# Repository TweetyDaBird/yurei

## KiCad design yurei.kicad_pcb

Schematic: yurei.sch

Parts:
C9: 4u7; C_0603_1608Metric; Manufacturer_Part_Number 06035C104JAT2A; Mouser Part Number 581-06035C104JAT2A
C10: C_Small; C_0805_2012Metric
C11: 22nF; C_0805_2012Metric
D1, D2, D3, D4, D5, D6, D7, D8, D9, D10, D11, D12, D13, D14, D15, D16, D17, D18, D19, D20, D21, D22, D23, D24, D25, D26, D27, D28, D29, D30, D31, D32, D33, D34, D35, D36, D37, D38, D39, D40, D41, D42, D43, D44, D45, D46, D47, D48, D49, D50, D51, D52, D53, D54, D55, D56, D57, D58, D59, D60, D61, D62, D63, D64, D65, D66, D67, D68, D69, D70, D71, D72, D73, D74, D75, D76, D77, D78, D79, D80, D81, D82, D83, D84, D85, D86, D87, D89: 1N4148W; D_SOD-123
D88: NSR0340HT1G; D_SOD-323; Manufacturer_Part_Number NSR0240HT1G
FT1: SI2301CDS-T1-GE3; SOT-23; Mouser Part Number 771-NX2301P215
H1: MountingHole_Pad; MountingHole_2.7mm_M2.5_DIN965_Pad
J1: Conn_01x02; PinHeader_1x02_P2.54mm_Vertical
J2: Conn_01x05; PinHeader_1x05_P2.54mm_Vertical
L1: L; L_0805_2012Metric
P1: USB_C_USB2.0; HRO-TYPE-C-31-M-12-Assembly
R1, R2: 5k1; R_0805_2012Metric_Pad1.15x1.40mm_HandSolder
R3: 1M; R_0805_2012Metric_Pad1.15x1.40mm_HandSolder
R5: 3K3; R_0402_1005Metric; Manufacturer_Part_Number 0402WGF3301TCE
R8: 10M; R_0402_1005Metric; Manufacturer_Part_Number 0402WGF3301TCE
R9: 2M2; R_0402_1005Metric; Manufacturer_Part_Number 0402WGF3301TCE
SW1, SW2, SW3, SW4, SW5, SW6, SW7, SW8, SW9, SW10, SW11, SW12, SW13, SW14, SW15, SW16, SW17, SW18, SW19, SW20, SW21, SW22, SW23, SW24, SW25, SW26, SW27, SW28, SW29, SW30, SW31, SW32, SW33, SW34, SW35, SW36, SW37, SW38, SW39, SW40, SW41, SW42, SW43, SW44, SW45, SW46, SW47, SW48, SW49, SW50, SW51, SW52, SW53, SW54, SW55, SW56, SW57, SW58, SW59, SW60, SW61, SW62, SW63, SW64, SW65, SW66, SW67, SW68, SW69, SW70, SW71, SW72, SW73, SW74, SW75, SW76, SW77, SW78, SW79, SW80, SW81, SW82, SW83, SW84, SW85, SW86, SW87, SW89, SW90: SW_SPST; Kailh_socket_MX_RGB
SW88: SW_Push
U1: TP4056_Charger; T4056 1A Charge
U3: E73-2G4M08S1C-52840

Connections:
BATT_MON: C11.1, R8.1, R9.1, U3.18
Batt+: J1.1, R8.2, U1.5 (Batt+)
Batt-: J1.2, U1.4 (Batt-)
Col0: SW1.1, SW17.1, SW34.1, SW51.1, SW64.1, SW77.1, SW90.2, U3.6
Col1: SW18.1, SW35.1, SW52.1, SW78.1, SW89.1, U3.7
Col2: SW2.1, SW19.1, SW36.1, SW53.1, SW65.1, SW79.1, U3.8
Col3: SW3.1, SW20.1, SW37.1, SW54.1, SW66.1, U3.9
Col4: SW4.1, SW21.1, SW38.1, SW55.1, SW67.1, U3.10
Col5: SW5.1, SW22.1, SW39.1, SW56.1, SW68.1, U3.20
Col6: SW6.1, SW23.1, SW40.1, SW57.1, SW69.1, SW80.1, U3.11
Col7: SW7.1, SW24.1, SW41.1, SW58.1, SW70.1, U3.12
Col8: SW8.1, SW25.1, SW42.1, SW59.1, SW71.1, U3.13
Col9: SW9.1, SW26.1, SW43.1, SW60.1, SW72.1, U3.14
Col10: SW10.1, SW27.1, SW44.1, SW61.1, SW73.1, SW81.1, U3.15
Col11: SW11.1, SW28.1, SW45.1, SW62.1, SW74.1, SW82.1, U3.16
Col12: SW12.1, SW29.1, SW46.1, SW75.1, SW83.1, U3.17
Col13: SW13.1, SW30.1, SW47.1, SW63.1, SW84.1, U3.4
Col14: SW14.1, SW31.1, SW48.1, SW85.1, U3.3
Col15: SW15.1, SW32.1, SW49.1, SW76.1, SW86.1, U3.2
Col16: SW16.1, SW33.1, SW50.1, SW87.1, U3.1
D+: P1.A6 (D+), P1.B6 (D+), U3.31
D-: P1.A7 (D-), P1.B7 (D-), U3.29
I2C+: U3.43; also elsewhere on the board
I2C-: U3.42; also elsewhere on the board
INTB: U3.41; also elsewhere on the board
Load: FT1.3 (D), U1.6 (Load+)
unnamed: D1.2, SW1.2
unnamed: D2.2, SW2.2
unnamed: D3.2, SW3.2
unnamed: D4.2, SW4.2
unnamed: D5.2, SW5.2
unnamed: D6.2, SW6.2
unnamed: D7.2, SW7.2
unnamed: D8.2, SW8.2
unnamed: D9.2, SW9.2
unnamed: D10.2, SW10.2
unnamed: D11.2, SW11.2
unnamed: D12.2, SW12.2
unnamed: D13.2, SW13.2
unnamed: D14.2, SW14.2
unnamed: D15.2, SW15.2
unnamed: D16.2, SW16.2
unnamed: D17.2, SW17.2
unnamed: D18.2, SW18.2
unnamed: D19.2, SW19.2
unnamed: D20.2, SW20.2
unnamed: D21.2, SW21.2
unnamed: D22.2, SW22.2
unnamed: D23.2, SW23.2
unnamed: D24.2, SW24.2
unnamed: D25.2, SW25.2
unnamed: D26.2, SW26.2
unnamed: D27.2, SW27.2
unnamed: D28.2, SW28.2
unnamed: D29.2, SW29.2
unnamed: D30.2, SW30.2
unnamed: D31.2, SW31.2
unnamed: D32.2, SW32.2
unnamed: D33.2, SW33.2
unnamed: D34.2, SW34.2
unnamed: D35.2, SW35.2
unnamed: D36.2, SW36.2
unnamed: D37.2 (A), SW37.2
unnamed: D38.2, SW38.2
unnamed: D39.2, SW39.2
unnamed: D40.2, SW40.2
unnamed: D41.2, SW41.2
unnamed: D42.2, SW42.2
unnamed: D43.2, SW43.2
unnamed: D44.2, SW44.2
unnamed: D45.2, SW45.2
unnamed: D46.2, SW46.2
unnamed: D47.2, SW47.2
unnamed: D48.2, SW48.2
unnamed: D49.2, SW49.2
unnamed: D50.2, SW50.2
unnamed: D51.2, SW51.2
unnamed: D52.2, SW52.2
unnamed: D53.2, SW53.2
unnamed: D54.2, SW54.2
unnamed: D55.2, SW55.2
unnamed: D56.2, SW56.2
unnamed: D57.2, SW57.2
unnamed: D58.2, SW58.2
unnamed: D59.2, SW59.2
unnamed: D60.2, SW60.2
unnamed: D61.2, SW61.2
unnamed: D62.2, SW62.2
unnamed: D63.2, SW63.2
unnamed: D64.2, SW64.2, SW90.1
unnamed: D65.2, SW65.2
unnamed: D66.2, SW66.2
unnamed: D67.2, SW67.2
unnamed: D68.2, SW68.2
unnamed: D69.2, SW69.2
unnamed: D70.2, SW70.2
unnamed: D71.2, SW71.2
unnamed: D72.2, SW72.2
unnamed: D73.2, SW73.2
unnamed: D74.2, SW74.2
unnamed: D75.2, SW75.2
unnamed: D76.2, SW76.2
unnamed: D77.2, SW77.2
unnamed: D78.2, SW78.2
unnamed: D79.2, SW79.2
unnamed: D80.2, SW80.2
unnamed: D81.2, SW81.2
unnamed: D82.2, SW82.2
unnamed: D83.2, SW83.2
unnamed: D84.2, SW84.2
unnamed: D85.2, SW85.2
unnamed: D86.2, SW86.2
unnamed: D87.2, SW87.2
unnamed: D89.2, SW89.2
unnamed: L1.2, U3.25
unnamed: P1.A5 (CC1), R1.2
unnamed: P1.B5 (CC2), R2.2
PWR: D88.1 (K), FT1.2 (S), U3.23; also elsewhere on the board
Reset: J2.4, SW88.1, U3.26
Row0: D1.1, D2.1, D3.1, D4.1, D5.1, D6.1, D7.1, D8.1, D9.1, D10.1, D11.1, D12.1, D13.1, D14.1, D15.1, D16.1, U3.30
Row1: D17.1, D18.1, D19.1, D20.1, D21.1, D22.1, D23.1, D24.1, D25.1, D26.1, D27.1, D28.1, D29.1, D30.1, D31.1, D32.1, D33.1, U3.32
Row2: D34.1, D35.1, D36.1, D37.1 (K), D38.1, D39.1, D40.1, D41.1, D42.1, D43.1, D44.1, D45.1, D46.1, D47.1, D48.1, D49.1, D50.1, U3.28
Row3: D51.1, D52.1, D53.1, D54.1, D55.1, D56.1, D57.1, D58.1, D59.1, D60.1, D61.1, D62.1, D63.1, U3.34
Row4: D64.1, D65.1, D66.1, D67.1, D68.1, D69.1, D70.1, D71.1, D72.1, D73.1, D74.1, D75.1, D76.1, D89.1, U3.38
Row5: D77.1, D78.1, D79.1, D80.1, D81.1, D82.1, D83.1, D84.1, D85.1, D86.1, D87.1, U3.36
SDB: U3.40; also elsewhere on the board
SHIELD: C9.1, H1.1, P1.S1 (SHIELD), R3.2
SWDCLK: J2.2, U3.39
SWDIO: J2.3, U3.37
VBUS: D88.2 (A), FT1.1 (G), P1.A4 (VBUS), P1.A9 (VBUS), P1.B4 (VBUS), P1.B9 (VBUS), R5.1, U1.1 (+5V), U3.27
V_IO: C10.1, J2.5, L1.1, U3.19; also elsewhere on the board

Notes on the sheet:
Battery charge/protection module (100/500/1000mA)
Footprint needs to be confirmed!
If case and/or plate is conductive, connect to shield for ESD/EMC protection. NOTE! Full metal case is NOT recommended for wireless/BT operation!
Power selector, isolates battery and charger from main circuit when USB cable is inserted.
separate power from charger with zener? diode (no backfeed!) switch??? för BT vs WL2.4Ghz
Rprog 10k - 130mA 5k - 250mA 4k - 300mA 3k - 400mA 2k - 580mA 1,66 - 690mA 1,5k - 780mA 1,33 - 900mA 1,2k - 1000mA
Battery voltage monitor
J-Link connector
Reset switch

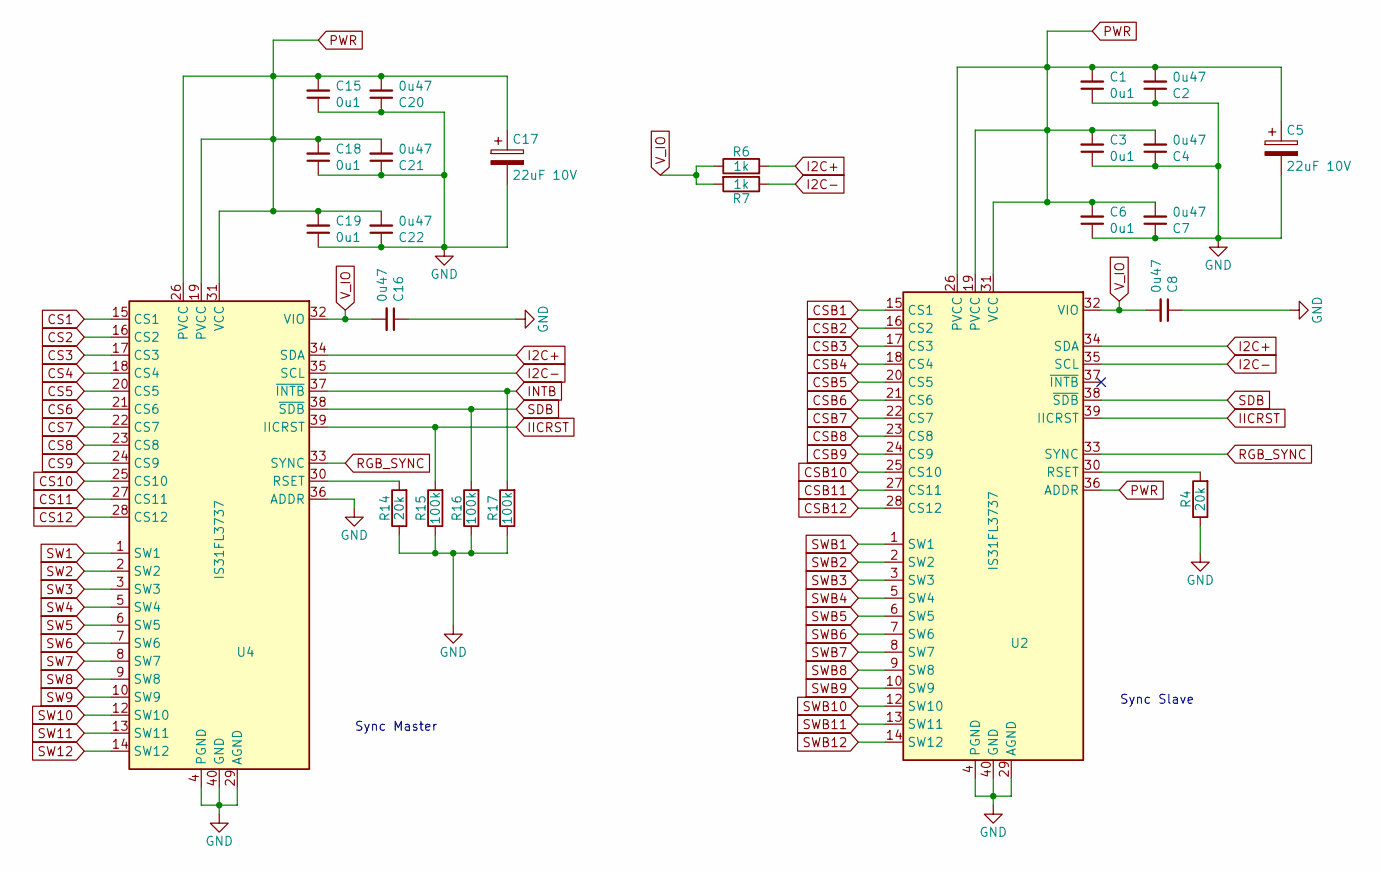
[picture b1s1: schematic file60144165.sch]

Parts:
C1, C3, C6, C15, C18, C19: 0u1; C_0603_1608Metric; Manufacturer_Part_Number 06035C104JAT2A; Mouser Part Number 581-06035C104JAT2A
C2, C4, C7, C8, C16, C20, C21, C22: 0u47; C_0603_1608Metric; Manufacturer_Part_Number UMK107B7474KA-TR; Mouser Part Number 963-UMK107B7474KA-TR
C5, C17: 22uF 10V; CP_EIA-3216-18_Kemet-A; Manufacturer_Part_Number TPSA226K010T0900; Mouser Part Number 581-TPSA226K010T0900
R4, R14: 20k; R_0603_1608Metric; Manufacturer_Part_Number ERJ-3GEYJ203V; Mouser Part Number 667-ERJ-3GEYJ203V
R6, R7: 1k; R_0603_1608Metric; Manufacturer_Part_Number ERJ-3EKF1003V; Mouser Part Number 667-ERJ-3EKF1003V
R15, R16, R17: 100k; R_0603_1608Metric; Manufacturer_Part_Number ERJ-3EKF1003V; Mouser Part Number 667-ERJ-3EKF1003V
U2, U4: IS31FL3737; QFN-40-1EP_5x5mm_P0.4mm_EP3.8x3.8mm_ThermalVias; Mouser Part Number 870-IS31FL3733-TQLS4

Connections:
CS1: U4.15 (CS1); also elsewhere on the board
CS2: U4.16 (CS2); also elsewhere on the board
CS3: U4.17 (CS3); also elsewhere on the board
CS4: U4.18 (CS4); also elsewhere on the board
CS5: U4.20 (CS5); also elsewhere on the board
CS6: U4.21 (CS6); also elsewhere on the board
CS7: U4.22 (CS7); also elsewhere on the board
CS8: U4.23 (CS8); also elsewhere on the board
CS9: U4.24 (CS9); also elsewhere on the board
CS10: U4.25 (CS10); also elsewhere on the board
CS11: U4.27 (CS11); also elsewhere on the board
CS12: U4.28 (CS12); also elsewhere on the board
CSB1: U2.15 (CS1); also elsewhere on the board
CSB2: U2.16 (CS2); also elsewhere on the board
CSB3: U2.17 (CS3); also elsewhere on the board
CSB4: U2.18 (CS4); also elsewhere on the board
CSB5: U2.20 (CS5); also elsewhere on the board
CSB6: U2.21 (CS6); also elsewhere on the board
CSB7: U2.22 (CS7); also elsewhere on the board
CSB8: U2.23 (CS8); also elsewhere on the board
CSB9: U2.24 (CS9); also elsewhere on the board
CSB10: U2.25 (CS10); also elsewhere on the board
CSB11: U2.27 (CS11); also elsewhere on the board
CSB12: U2.28 (CS12); also elsewhere on the board
I2C+: R6.2, U2.34 (SDA), U4.34 (SDA); also elsewhere on the board
I2C-: R7.1, U2.35 (SCL), U4.35 (SCL); also elsewhere on the board
IICRST: R15.2, U2.39 (IICRST), U4.39 (IICRST)
INTB: R17.2, U4.37 (~INTB); also elsewhere on the board
unnamed: R4.2, U2.30 (RSET)
unnamed: R14.2, U4.30 (RSET)
PWR: C1.2, C2.2, C3.2, C4.2, C5.1, C6.2, C7.2, C15.2, C17.1, C18.2, C19.2, C20.2, C21.2, C22.2, U2.19 (PVCC), U2.26 (PVCC), U2.31 (VCC), U2.36 (ADDR), U4.19 (PVCC), U4.26 (PVCC), U4.31 (VCC); also elsewhere on the board
RGB_SYNC: U2.33 (SYNC), U4.33 (SYNC)
SDB: R16.2, U2.38 (~SDB), U4.38 (~SDB); also elsewhere on the board
SW1: U4.1 (SW1); also elsewhere on the board
SW2: U4.2 (SW2); also elsewhere on the board
SW3: U4.3 (SW3); also elsewhere on the board
SW4: U4.5 (SW4); also elsewhere on the board
SW5: U4.6 (SW5); also elsewhere on the board
SW6: U4.7 (SW6); also elsewhere on the board
SW7: U4.8 (SW7); also elsewhere on the board
SW8: U4.9 (SW8); also elsewhere on the board
SW9: U4.10 (SW9); also elsewhere on the board
SW10: U4.12 (SW10); also elsewhere on the board
SW11: U4.13 (SW11); also elsewhere on the board
SW12: U4.14 (SW12); also elsewhere on the board
SWB1: U2.1 (SW1); also elsewhere on the board
SWB2: U2.2 (SW2); also elsewhere on the board
SWB3: U2.3 (SW3); also elsewhere on the board
SWB4: U2.5 (SW4); also elsewhere on the board
SWB5: U2.6 (SW5); also elsewhere on the board
SWB6: U2.7 (SW6); also elsewhere on the board
SWB7: U2.8 (SW7); also elsewhere on the board
SWB8: U2.9 (SW8); also elsewhere on the board
SWB9: U2.10 (SW9); also elsewhere on the board
SWB10: U2.12 (SW10); also elsewhere on the board
SWB11: U2.13 (SW11); also elsewhere on the board
SWB12: U2.14 (SW12); also elsewhere on the board
V_IO: C8.2, C16.2, R6.1, R7.2, U2.32 (VIO), U4.32 (VIO); also elsewhere on the board

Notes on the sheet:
Sync Master
Sync Slave

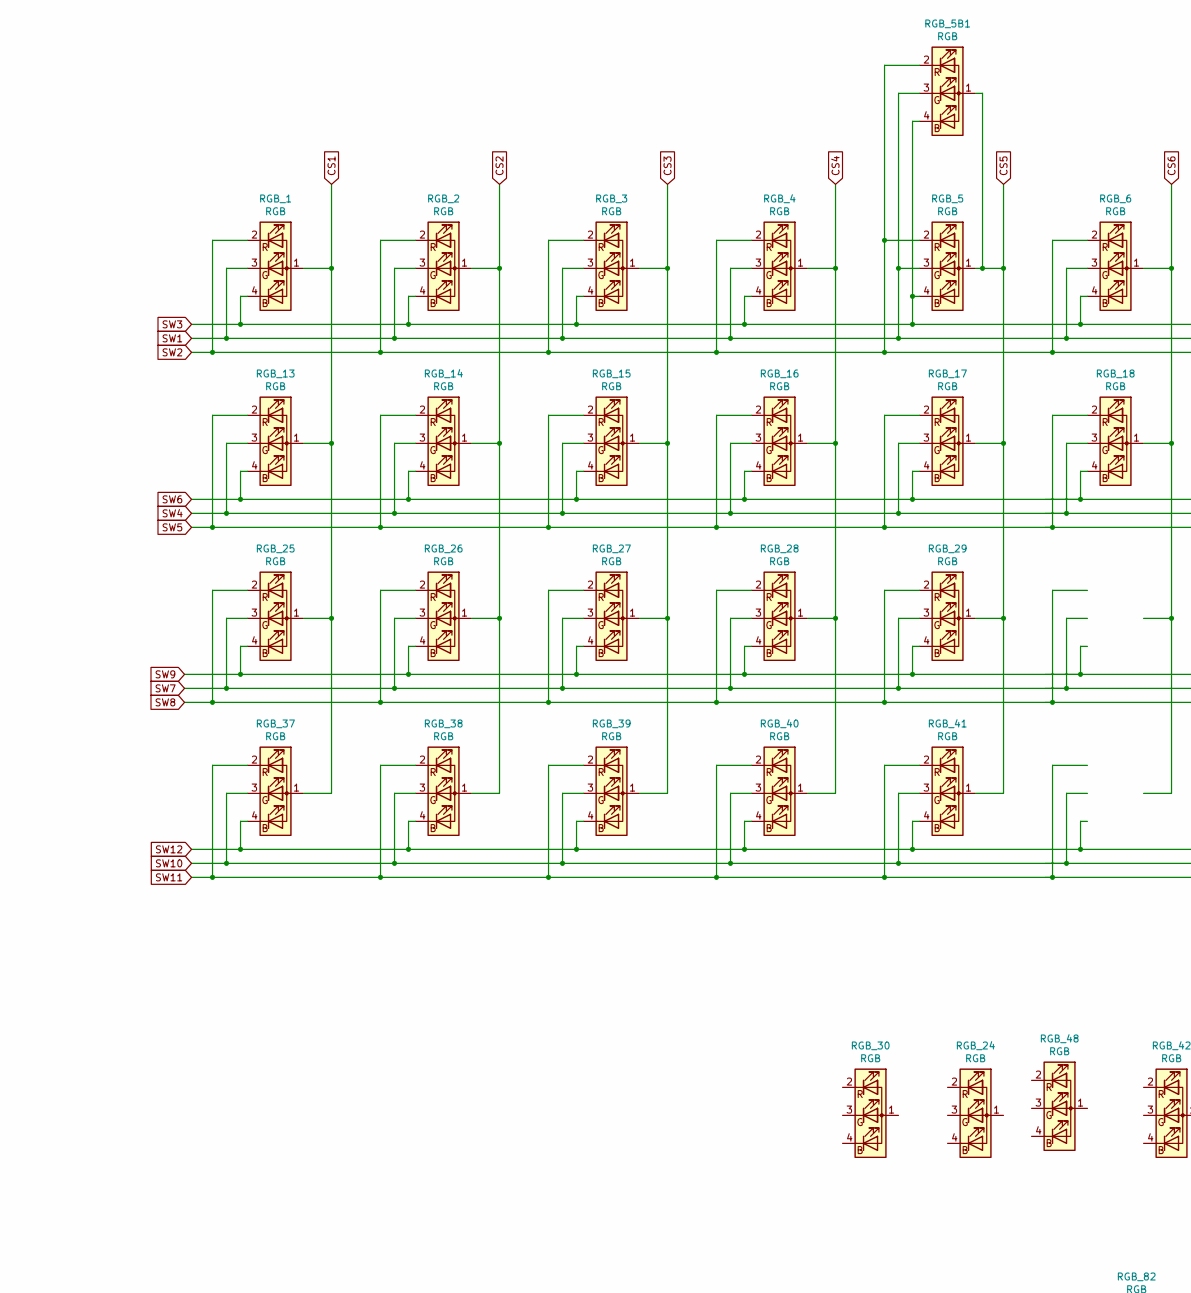
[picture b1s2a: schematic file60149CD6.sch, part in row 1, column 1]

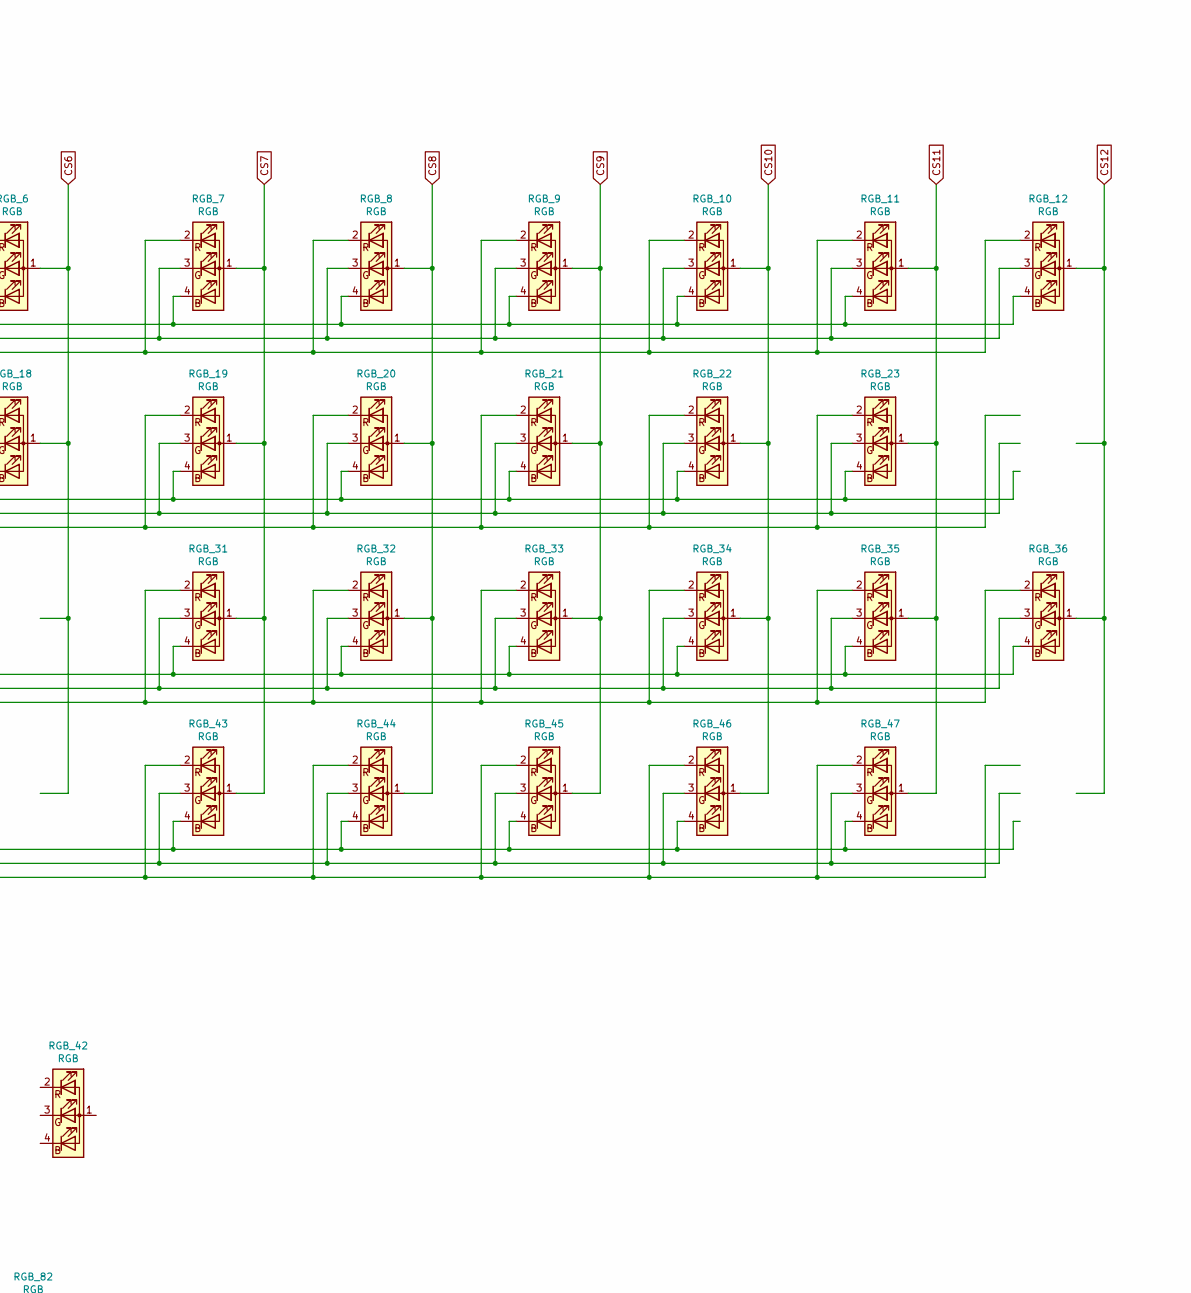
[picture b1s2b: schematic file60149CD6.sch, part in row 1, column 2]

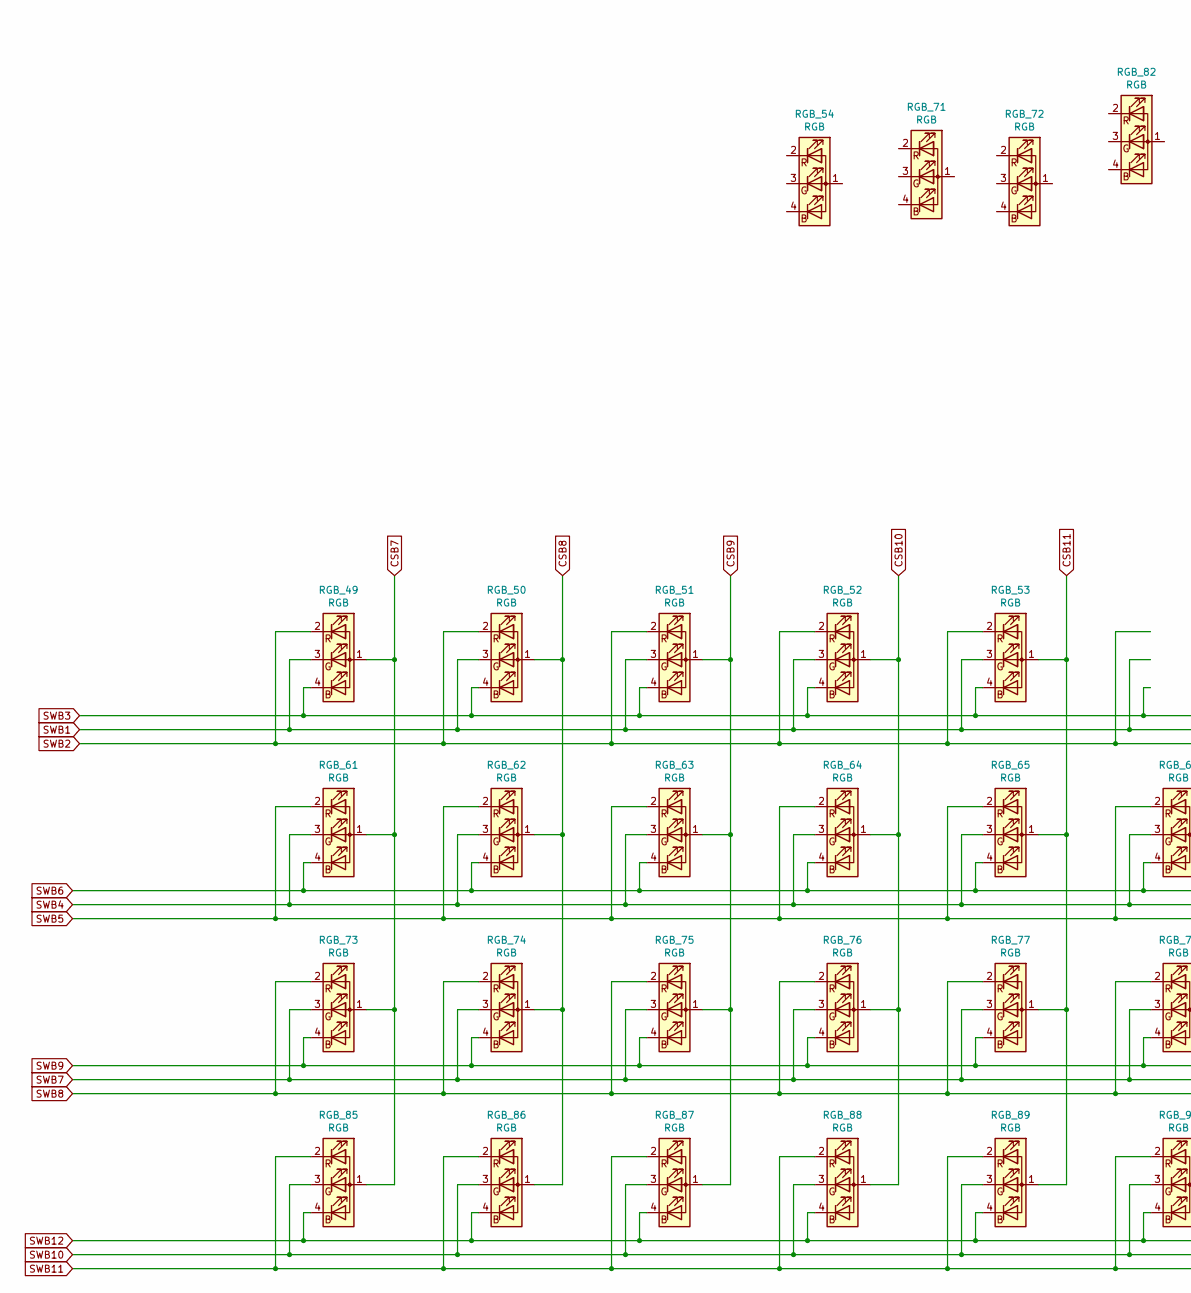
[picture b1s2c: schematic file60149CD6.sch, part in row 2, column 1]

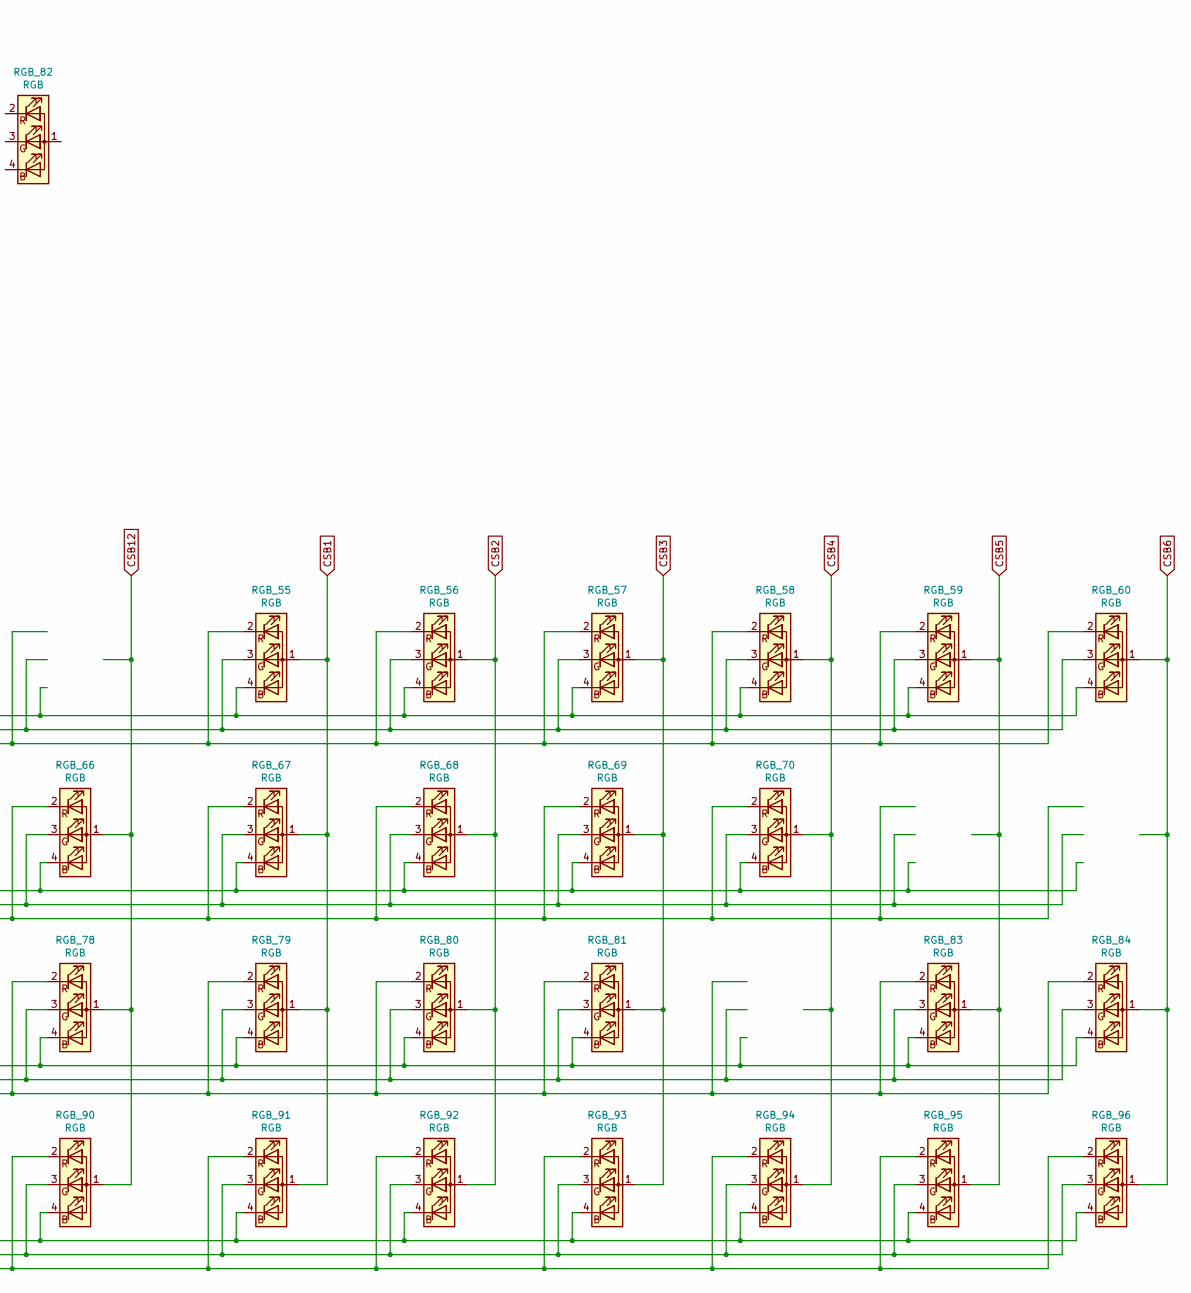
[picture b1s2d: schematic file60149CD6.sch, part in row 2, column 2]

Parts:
RGB_1, RGB_2, RGB_3, RGB_4, RGB_5, RGB_5B1, RGB_6, RGB_7, RGB_8, RGB_9, RGB_10, RGB_11, RGB_12, RGB_13, RGB_14, RGB_15, RGB_16, RGB_17, RGB_18, RGB_19, RGB_20, RGB_21, RGB_22, RGB_23, RGB_24, RGB_25, RGB_26, RGB_27, RGB_28, RGB_29, RGB_30, RGB_31, RGB_32, RGB_33, RGB_34, RGB_35, RGB_36, RGB_37, RGB_38, RGB_39, RGB_40, RGB_41, RGB_42, RGB_43, RGB_44, RGB_45, RGB_46, RGB_47, RGB_48, RGB_49, RGB_50, RGB_51, RGB_52, RGB_53, RGB_54, RGB_55, RGB_56, RGB_57, RGB_58, RGB_59, RGB_60, RGB_61, RGB_62, RGB_63, RGB_64, RGB_65, RGB_66, RGB_67, RGB_68, RGB_69, RGB_70, RGB_71, RGB_72, RGB_73, RGB_74, RGB_75, RGB_76, RGB_77, RGB_78, RGB_79, RGB_80, RGB_81, RGB_82, RGB_83, RGB_84, RGB_85, RGB_86, RGB_87, RGB_88, RGB_89, RGB_90, RGB_91, RGB_92, RGB_93, RGB_94, RGB_95, RGB_96: RGB; APTF1616SEEZGQBDC; Mouser Part Number 604-APTF1616SEJ3ZGGV

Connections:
CS1: RGB_1.1 (A), RGB_13.1 (A), RGB_25.1 (A), RGB_37.1 (A); also elsewhere on the board
CS2: RGB_2.1 (A), RGB_14.1 (A), RGB_26.1 (A), RGB_38.1 (A); also elsewhere on the board
CS3: RGB_3.1 (A), RGB_15.1 (A), RGB_27.1 (A), RGB_39.1 (A); also elsewhere on the board
CS4: RGB_4.1 (A), RGB_16.1 (A), RGB_28.1 (A), RGB_40.1 (A); also elsewhere on the board
CS5: RGB_5.1 (A), RGB_5B1.1 (A), RGB_17.1 (A), RGB_29.1 (A), RGB_41.1 (A); also elsewhere on the board
CS6: RGB_6.1 (A), RGB_18.1 (A); also elsewhere on the board
CS7: RGB_7.1 (A), RGB_19.1 (A), RGB_31.1 (A), RGB_43.1 (A); also elsewhere on the board
CS8: RGB_8.1 (A), RGB_20.1 (A), RGB_32.1 (A), RGB_44.1 (A); also elsewhere on the board
CS9: RGB_9.1 (A), RGB_21.1 (A), RGB_33.1 (A), RGB_45.1 (A); also elsewhere on the board
CS10: RGB_10.1 (A), RGB_22.1 (A), RGB_34.1 (A), RGB_46.1 (A); also elsewhere on the board
CS11: RGB_11.1 (A), RGB_23.1 (A), RGB_35.1 (A), RGB_47.1 (A); also elsewhere on the board
CS12: RGB_12.1 (A), RGB_36.1 (A); also elsewhere on the board
CSB1: RGB_55.1 (A), RGB_67.1 (A), RGB_79.1 (A), RGB_91.1 (A); also elsewhere on the board
CSB2: RGB_56.1 (A), RGB_68.1 (A), RGB_80.1 (A), RGB_92.1 (A); also elsewhere on the board
CSB3: RGB_57.1 (A), RGB_69.1 (A), RGB_81.1 (A), RGB_93.1 (A); also elsewhere on the board
CSB4: RGB_58.1 (A), RGB_70.1 (A), RGB_94.1 (A); also elsewhere on the board
CSB5: RGB_59.1 (A), RGB_83.1 (A), RGB_95.1 (A); also elsewhere on the board
CSB6: RGB_60.1 (A), RGB_84.1 (A), RGB_96.1 (A); also elsewhere on the board
CSB7: RGB_49.1 (A), RGB_61.1 (A), RGB_73.1 (A), RGB_85.1 (A); also elsewhere on the board
CSB8: RGB_50.1 (A), RGB_62.1 (A), RGB_74.1 (A), RGB_86.1 (A); also elsewhere on the board
CSB9: RGB_51.1 (A), RGB_63.1 (A), RGB_75.1 (A), RGB_87.1 (A); also elsewhere on the board
CSB10: RGB_52.1 (A), RGB_64.1 (A), RGB_76.1 (A), RGB_88.1 (A); also elsewhere on the board
CSB11: RGB_53.1 (A), RGB_65.1 (A), RGB_77.1 (A), RGB_89.1 (A); also elsewhere on the board
CSB12: RGB_66.1 (A), RGB_78.1 (A), RGB_90.1 (A); also elsewhere on the board
SW1: RGB_1.3 (GK), RGB_2.3 (GK), RGB_3.3 (GK), RGB_4.3 (GK), RGB_5.3 (GK), RGB_5B1.3 (GK), RGB_6.3 (GK), RGB_7.3 (GK), RGB_8.3 (GK), RGB_9.3 (GK), RGB_10.3 (GK), RGB_11.3 (GK), RGB_12.3 (GK); also elsewhere on the board
SW2: RGB_1.2 (RK), RGB_2.2 (RK), RGB_3.2 (RK), RGB_4.2 (RK), RGB_5.2 (RK), RGB_5B1.2 (RK), RGB_6.2 (RK), RGB_7.2 (RK), RGB_8.2 (RK), RGB_9.2 (RK), RGB_10.2 (RK), RGB_11.2 (RK), RGB_12.2 (RK); also elsewhere on the board
SW3: RGB_1.4 (BK), RGB_2.4 (BK), RGB_3.4 (BK), RGB_4.4 (BK), RGB_5.4 (BK), RGB_5B1.4 (BK), RGB_6.4 (BK), RGB_7.4 (BK), RGB_8.4 (BK), RGB_9.4 (BK), RGB_10.4 (BK), RGB_11.4 (BK), RGB_12.4 (BK); also elsewhere on the board
SW4: RGB_13.3 (GK), RGB_14.3 (GK), RGB_15.3 (GK), RGB_16.3 (GK), RGB_17.3 (GK), RGB_18.3 (GK), RGB_19.3 (GK), RGB_20.3 (GK), RGB_21.3 (GK), RGB_22.3 (GK), RGB_23.3 (GK); also elsewhere on the board
SW5: RGB_13.2 (RK), RGB_14.2 (RK), RGB_15.2 (RK), RGB_16.2 (RK), RGB_17.2 (RK), RGB_18.2 (RK), RGB_19.2 (RK), RGB_20.2 (RK), RGB_21.2 (RK), RGB_22.2 (RK), RGB_23.2 (RK); also elsewhere on the board
SW6: RGB_13.4 (BK), RGB_14.4 (BK), RGB_15.4 (BK), RGB_16.4 (BK), RGB_17.4 (BK), RGB_18.4 (BK), RGB_19.4 (BK), RGB_20.4 (BK), RGB_21.4 (BK), RGB_22.4 (BK), RGB_23.4 (BK); also elsewhere on the board
SW7: RGB_25.3 (GK), RGB_26.3 (GK), RGB_27.3 (GK), RGB_28.3 (GK), RGB_29.3 (GK), RGB_31.3 (GK), RGB_32.3 (GK), RGB_33.3 (GK), RGB_34.3 (GK), RGB_35.3 (GK), RGB_36.3 (GK); also elsewhere on the board
SW8: RGB_25.2 (RK), RGB_26.2 (RK), RGB_27.2 (RK), RGB_28.2 (RK), RGB_29.2 (RK), RGB_31.2 (RK), RGB_32.2 (RK), RGB_33.2 (RK), RGB_34.2 (RK), RGB_35.2 (RK), RGB_36.2 (RK); also elsewhere on the board
SW9: RGB_25.4 (BK), RGB_26.4 (BK), RGB_27.4 (BK), RGB_28.4 (BK), RGB_29.4 (BK), RGB_31.4 (BK), RGB_32.4 (BK), RGB_33.4 (BK), RGB_34.4 (BK), RGB_35.4 (BK), RGB_36.4 (BK); also elsewhere on the board
SW10: RGB_37.3 (GK), RGB_38.3 (GK), RGB_39.3 (GK), RGB_40.3 (GK), RGB_41.3 (GK), RGB_43.3 (GK), RGB_44.3 (GK), RGB_45.3 (GK), RGB_46.3 (GK), RGB_47.3 (GK); also elsewhere on the board
SW11: RGB_37.2 (RK), RGB_38.2 (RK), RGB_39.2 (RK), RGB_40.2 (RK), RGB_41.2 (RK), RGB_43.2 (RK), RGB_44.2 (RK), RGB_45.2 (RK), RGB_46.2 (RK), RGB_47.2 (RK); also elsewhere on the board
SW12: RGB_37.4 (BK), RGB_38.4 (BK), RGB_39.4 (BK), RGB_40.4 (BK), RGB_41.4 (BK), RGB_43.4 (BK), RGB_44.4 (BK), RGB_45.4 (BK), RGB_46.4 (BK), RGB_47.4 (BK); also elsewhere on the board
SWB1: RGB_49.3 (GK), RGB_50.3 (GK), RGB_51.3 (GK), RGB_52.3 (GK), RGB_53.3 (GK), RGB_55.3 (GK), RGB_56.3 (GK), RGB_57.3 (GK), RGB_58.3 (GK), RGB_59.3 (GK), RGB_60.3 (GK); also elsewhere on the board
SWB2: RGB_49.2 (RK), RGB_50.2 (RK), RGB_51.2 (RK), RGB_52.2 (RK), RGB_53.2 (RK), RGB_55.2 (RK), RGB_56.2 (RK), RGB_57.2 (RK), RGB_58.2 (RK), RGB_59.2 (RK), RGB_60.2 (RK); also elsewhere on the board
SWB3: RGB_49.4 (BK), RGB_50.4 (BK), RGB_51.4 (BK), RGB_52.4 (BK), RGB_53.4 (BK), RGB_55.4 (BK), RGB_56.4 (BK), RGB_57.4 (BK), RGB_58.4 (BK), RGB_59.4 (BK), RGB_60.4 (BK); also elsewhere on the board
SWB4: RGB_61.3 (GK), RGB_62.3 (GK), RGB_63.3 (GK), RGB_64.3 (GK), RGB_65.3 (GK), RGB_66.3 (GK), RGB_67.3 (GK), RGB_68.3 (GK), RGB_69.3 (GK), RGB_70.3 (GK); also elsewhere on the board
SWB5: RGB_61.2 (RK), RGB_62.2 (RK), RGB_63.2 (RK), RGB_64.2 (RK), RGB_65.2 (RK), RGB_66.2 (RK), RGB_67.2 (RK), RGB_68.2 (RK), RGB_69.2 (RK), RGB_70.2 (RK); also elsewhere on the board
SWB6: RGB_61.4 (BK), RGB_62.4 (BK), RGB_63.4 (BK), RGB_64.4 (BK), RGB_65.4 (BK), RGB_66.4 (BK), RGB_67.4 (BK), RGB_68.4 (BK), RGB_69.4 (BK), RGB_70.4 (BK); also elsewhere on the board
SWB7: RGB_73.3 (GK), RGB_74.3 (GK), RGB_75.3 (GK), RGB_76.3 (GK), RGB_77.3 (GK), RGB_78.3 (GK), RGB_79.3 (GK), RGB_80.3 (GK), RGB_81.3 (GK), RGB_83.3 (GK), RGB_84.3 (GK); also elsewhere on the board
SWB8: RGB_73.2 (RK), RGB_74.2 (RK), RGB_75.2 (RK), RGB_76.2 (RK), RGB_77.2 (RK), RGB_78.2 (RK), RGB_79.2 (RK), RGB_80.2 (RK), RGB_81.2 (RK), RGB_83.2 (RK), RGB_84.2 (RK); also elsewhere on the board
SWB9: RGB_73.4 (BK), RGB_74.4 (BK), RGB_75.4 (BK), RGB_76.4 (BK), RGB_77.4 (BK), RGB_78.4 (BK), RGB_79.4 (BK), RGB_80.4 (BK), RGB_81.4 (BK), RGB_83.4 (BK), RGB_84.4 (BK); also elsewhere on the board
SWB10: RGB_85.3 (GK), RGB_86.3 (GK), RGB_87.3 (GK), RGB_88.3 (GK), RGB_89.3 (GK), RGB_90.3 (GK), RGB_91.3 (GK), RGB_92.3 (GK), RGB_93.3 (GK), RGB_94.3 (GK), RGB_95.3 (GK), RGB_96.3 (GK); also elsewhere on the board
SWB11: RGB_85.2 (RK), RGB_86.2 (RK), RGB_87.2 (RK), RGB_88.2 (RK), RGB_89.2 (RK), RGB_90.2 (RK), RGB_91.2 (RK), RGB_92.2 (RK), RGB_93.2 (RK), RGB_94.2 (RK), RGB_95.2 (RK), RGB_96.2 (RK); also elsewhere on the board
SWB12: RGB_85.4 (BK), RGB_86.4 (BK), RGB_87.4 (BK), RGB_88.4 (BK), RGB_89.4 (BK), RGB_90.4 (BK), RGB_91.4 (BK), RGB_92.4 (BK), RGB_93.4 (BK), RGB_94.4 (BK), RGB_95.4 (BK), RGB_96.4 (BK); also elsewhere on the board

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
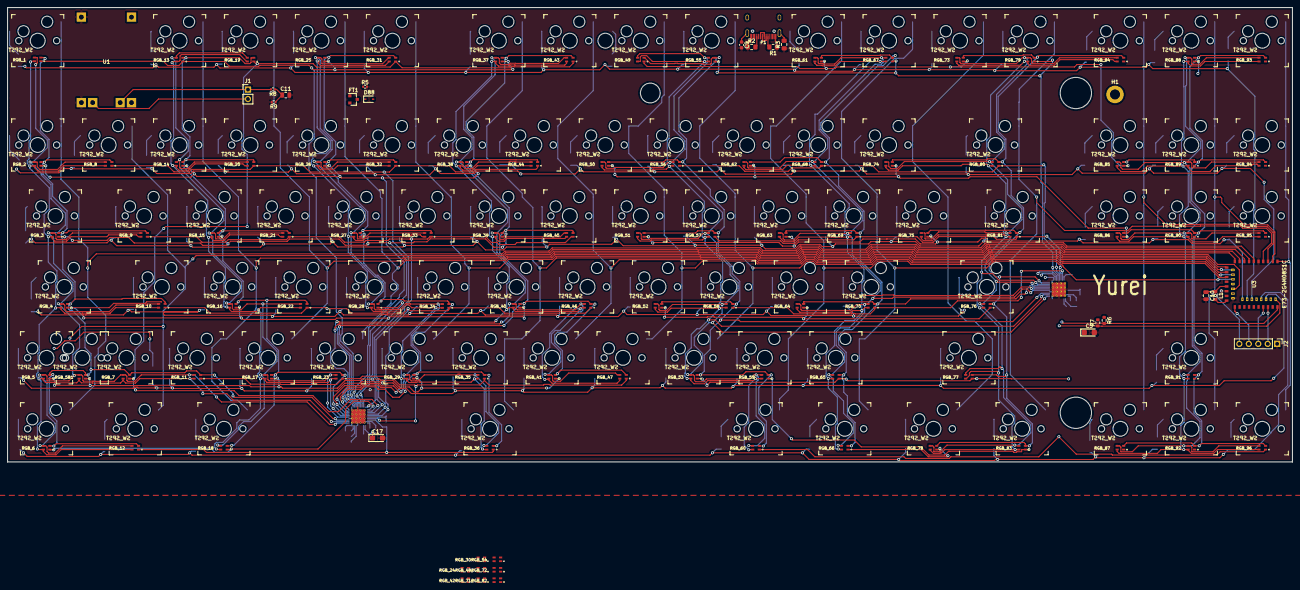
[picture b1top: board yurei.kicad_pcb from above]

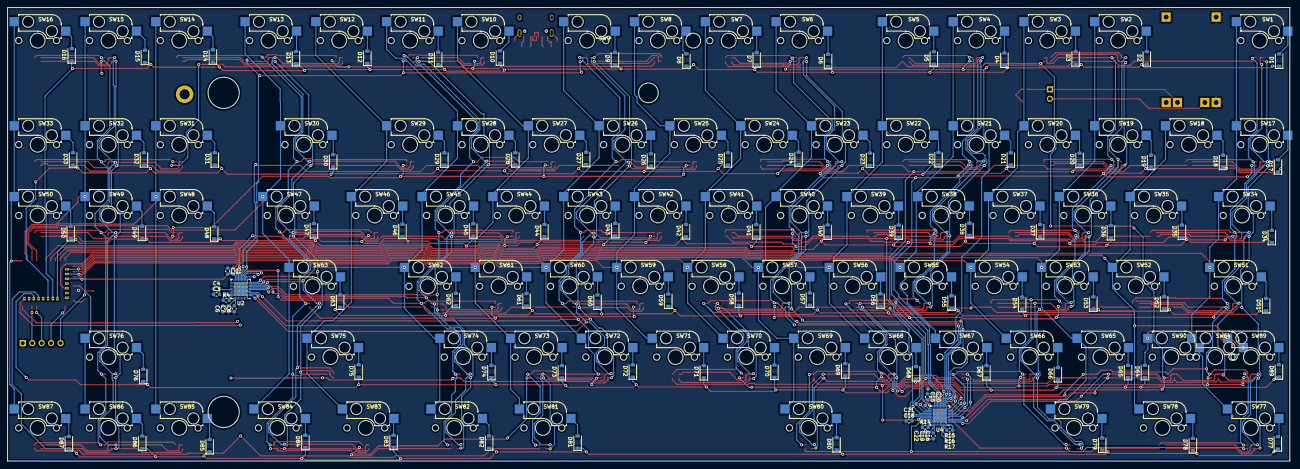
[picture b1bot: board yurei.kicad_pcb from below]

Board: 2 copper layers, 344.8 x 121.9 mm, 317 parts (109 on the bottom side), 184 nets.

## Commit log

2021-01-19 First edit
2021-01-23 Added wireless circuit
    nRF82840 wirelss module
    TP4056 Charging/loadshare
2021-02-12 test
